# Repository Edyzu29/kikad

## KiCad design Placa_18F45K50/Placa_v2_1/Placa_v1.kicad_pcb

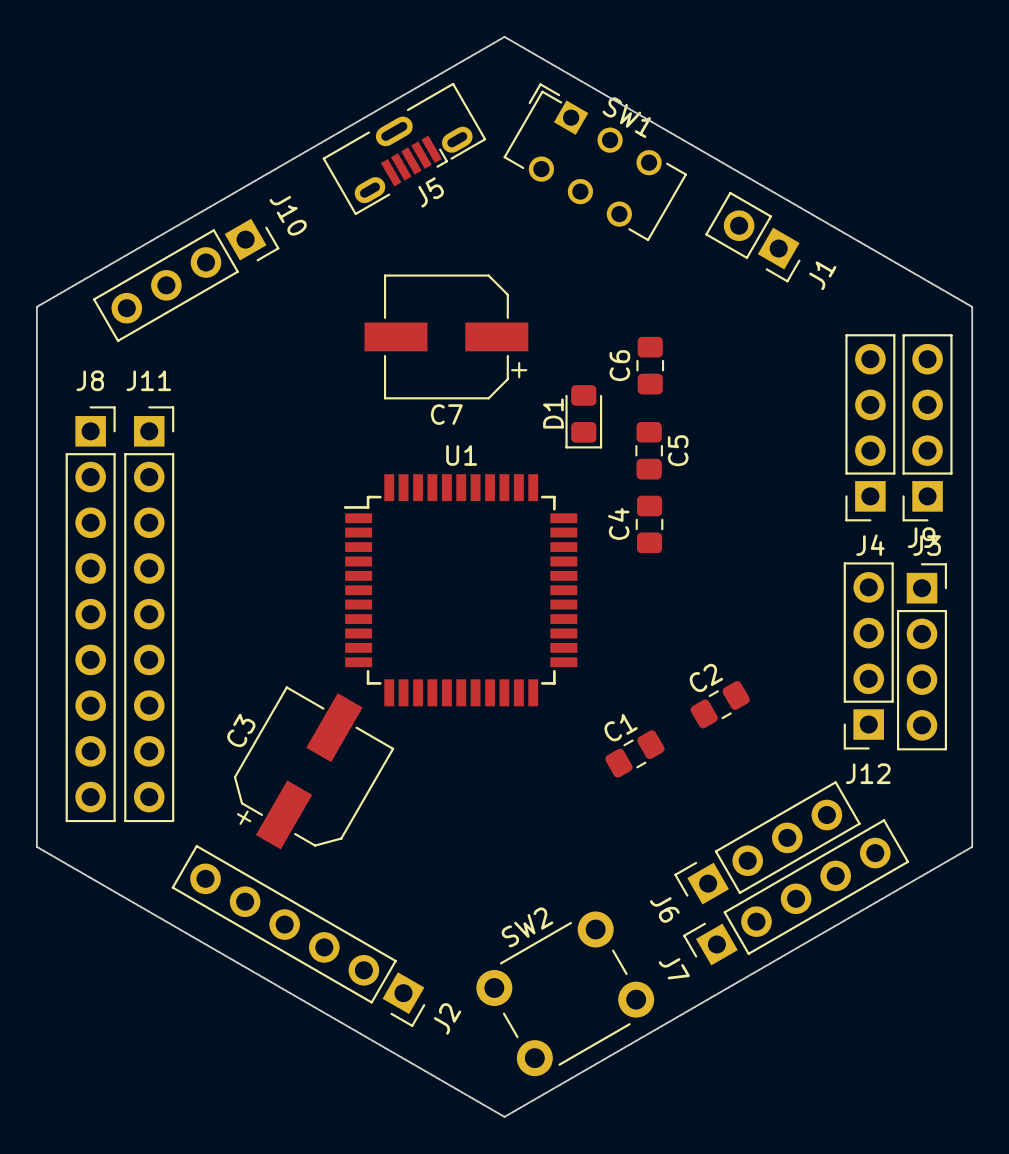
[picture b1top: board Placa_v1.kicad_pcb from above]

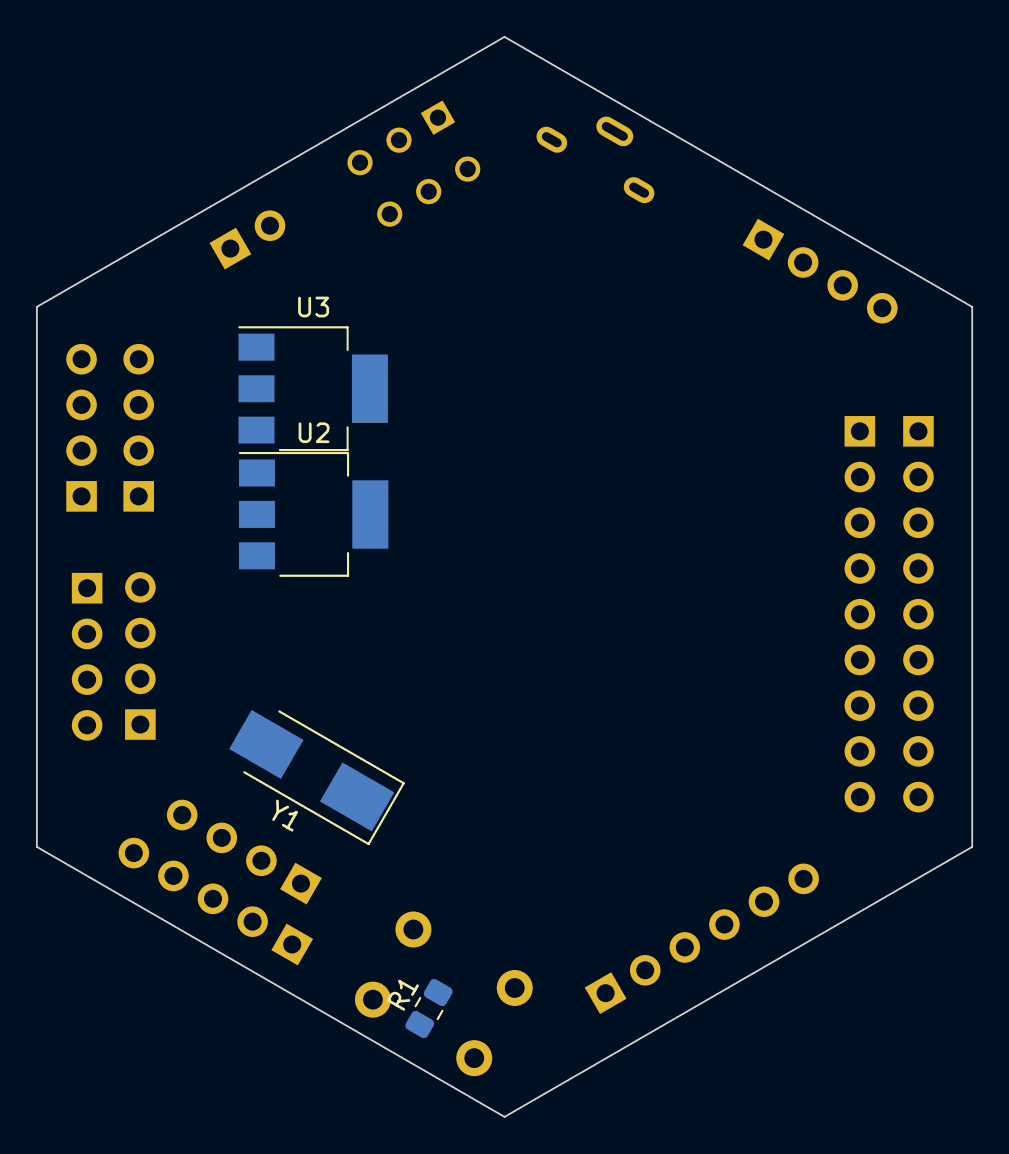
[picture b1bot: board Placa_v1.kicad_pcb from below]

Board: 2 copper layers, 52.0 x 60.0 mm, 27 parts (4 on the bottom side), 43 nets, no tracks yet.

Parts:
C1, C2: 22pf; C_0805_2012Metric_Pad1.15x1.40mm_HandSolder
C3: 100uF/25V; CP_Elec_6.3x5.4
C4, C5: C; C_0805_2012Metric_Pad1.15x1.40mm_HandSolder
C6: 104; C_0805_2012Metric_Pad1.15x1.40mm_HandSolder
C7: 47uF; CP_Elec_6.3x5.4
D1: D; D_0805_2012Metric_Pad1.15x1.40mm_HandSolder
J1: Bateria; PinSocket_1x02_P2.54mm_Vertical
J2: Pickit; PinSocket_1x06_P2.54mm_Vertical
J3: SOURCE 0; PinSocket_1x04_P2.54mm_Vertical
J4: SOURCE 1; PinSocket_1x04_P2.54mm_Vertical
J5: USB_B_Micro; USB_Micro-B_Molex-105133-0001
J6: PUERTO A0; PinSocket_1x04_P2.54mm_Vertical
J7: PUERTO A1; PinSocket_1x05_P2.54mm_Vertical
J8: PUERTO B; PinSocket_1x09_P2.54mm_Vertical
J9: PUERTO C; PinSocket_1x04_P2.54mm_Vertical
J10: BLUETOOTH; PinSocket_1x04_P2.54mm_Vertical
J11: PUERTO D; PinSocket_1x09_P2.54mm_Vertical
J12: PUERTO E; PinSocket_1x04_P2.54mm_Vertical
R1: R; R_0805_2012Metric_Pad1.15x1.40mm_HandSolder
SW1: SW_DPDT_x2; SW_CuK_JS202011CQN_DPDT_Straight
SW2: SW_Push; SW_PUSH_6mm
U1: PIC18F4550-IPT; TQFP-44_10x10mm_P0.8mm
U2, U3: AMS1117; SOT-223
Y1: Crystal; Crystal_SMD_0603-2Pin_6.0x3.5mm_HandSoldering

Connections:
/3V: C6.1, J3.3, J4.3, U3.2
/CLK1: C2.1, U1.30, Y1.2
/D+: J5.3, U1.43
/D-: J5.2, U1.42
/MCLR: J2.1, R1.1, SW2.2, U1.18
/PGC: J2.5, J8.8, U1.16
/PGD: J2.4, J8.9, U1.17
/PGM: J2.6, J8.7, U1.15
/RA0: J6.1, U1.19
/RA1: J7.3, U1.20
/RA2: J6.2, U1.21
/RA3: J7.4, U1.22
/RA4: J6.3, U1.23
/RA5: J7.5, U1.24
/RA6: C1.2, J6.4, U1.31, Y1.1
/RB0: J8.2, U1.8
/RB1: J8.3, U1.9
/RB2: J8.4, U1.10
/RB3: J8.5, U1.11
/RB4: J8.6, U1.14
/RC0: J9.2, U1.32
/RC1: J9.3, U1.35
/RC2: J9.4, U1.36
/RD0: J11.2, U1.38
/RD1: J11.3, U1.39
/RD2: J11.4, U1.40
/RD3: J11.5, U1.41
/RD4: J11.6, U1.2
/RD5: J11.7, U1.3
/RD6: J11.8, U1.4
/RD7: J11.9, U1.5
/RE0: J12.2, U1.25
/RE1: J12.3, U1.26
/RE2: J12.4, U1.27
/Rx: J10.2, U1.1
/Tx: J10.1, U1.44
/Va: J5.1, SW1.5
GND: C1.1, C2.2, C3.2, C4.2, C5.2, C6.2, C7.2, J1.1, J2.3, J3.2, J3.4, J4.2, J4.4, J5.4, J5.5, J5.6, J7.2, J8.1, J10.3, J12.1, SW2.1, U1.6, U1.29, U2.1, U3.1
unnamed: C4.1, D1.1, U2.3
unnamed: C7.1, U1.37
unnamed: D1.2, SW1.1
unnamed: J1.2, SW1.2
VCC: C3.1, C5.1, J2.2, J3.1, J4.1, J7.1, J9.1, J10.4, J11.1, R1.2, SW1.6, U1.7, U1.28, U2.2, U3.3

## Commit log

2021-04-21 subiendo todo
